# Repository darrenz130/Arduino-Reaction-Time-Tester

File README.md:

<h1>Arduino Reaction Time Tester PCB Design</h1>

<h2>Overview</h2>

<p>
This project is an Arduino-based reaction time testing system designed to measure human response speed with millisecond accuracy. The system uses LEDs as visual stimuli, a push button for user input, and a display to show reaction time results. The firmware is written in C++ and implemented on a custom PCB designed in KiCad.
</p>

<h2>Project Walkthrough</h2>

<h3>1. Breadboard Prototype</h3>

<p>
The initial version of the circuit was built and tested on a breadboard to validate functionality. This phase focused on verifying LED triggering, button input detection, and reaction timing accuracy.
</p>

<h3>2. Firmware Development</h3>

<p>
The system was programmed in C++ using the Arduino IDE. The code handles randomized LED stimulus timing, button press detection, and calculates reaction time in milliseconds using precise timing functions.
</p>

<h3>3. Schematic Design</h3>

<p>
A full circuit schematic was created in KiCad to define the electrical connections between the Arduino, LEDs, button, and display.
</p>

<h3>4. PCB Design</h3>

<p>
A custom PCB shield was designed in KiCad to replace the breadboard setup. This reduced wiring complexity, improved reliability, and created a compact final hardware design.
</p>

<p>
Custom footprints were created where required to match exact component dimensions. This included a potentiometer footprint due to the lack of an existing library part with the correct physical spacing, as well as a custom footprint for the display LED to ensure proper fit and alignment.
</p>

<h2>Languages and Tools Used</h2>

<ul>
  <li>C++</li>
  <li>Arduino IDE</li>
  <li>KiCad (PCB Design)</li>
  <li>Breadboard Prototyping</li>
  <li>Multimeter / Circuit Debugging</li>
</ul>

<h2>Files in This Repository</h2>

<ul>
  <li><b>/firmware</b> → Arduino C++ code</li>
  <li><b>/pcb</b> → KiCad schematic and PCB files</li>
  <li><b>/images</b> → Project screenshots and renders</li>
</ul>

<h2>Demo</h2>

<p>
A short demonstration of the system in action:
<br>
<a href="https://youtu.be/OleBV9ndicw?si=QzNY1ve2LQjAxAnz">
Watch Demo Video
</a>
</p>

<h2>Key Features</h2>

<ul>
  <li>Millisecond-level reaction time measurement</li>
  <li>Randomized LED stimulus timing</li>
  <li>Custom PCB shield for improved reliability</li>
  <li>Fully tested breadboard prototype before final design</li>
</ul>

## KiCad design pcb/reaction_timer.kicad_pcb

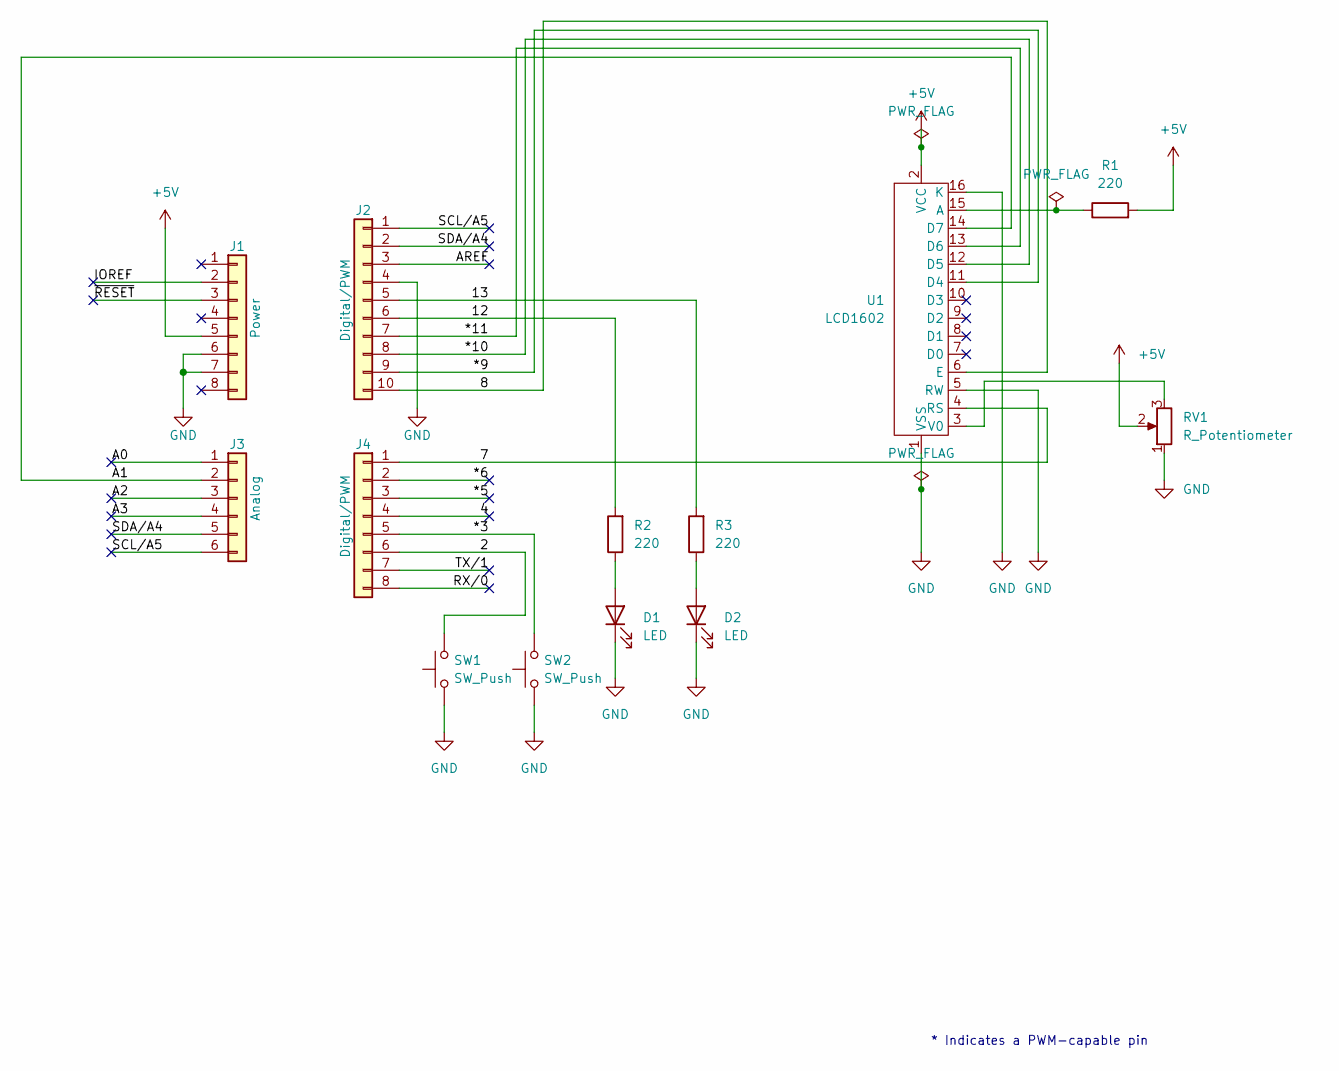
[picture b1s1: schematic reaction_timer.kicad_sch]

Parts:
D1, D2: LED; LED_D5.0mm
J1: Power; PinSocket_1x08_P2.54mm_Vertical
J2: Digital/PWM; PinSocket_1x10_P2.54mm_Vertical
J3: Analog; PinSocket_1x06_P2.54mm_Vertical
J4: Digital/PWM; PinSocket_1x08_P2.54mm_Vertical
R1, R2, R3: 220; R_Axial_DIN0207_L6.3mm_D2.5mm_P7.62mm_Horizontal
RV1: R_Potentiometer; 10k potentiameter
SW1, SW2: SW_Push; SW_PUSH_6mm
U1: LCD1602; PinSocket_1x16_P2.54mm_Vertical

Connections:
+5V: J1.5, R1.2, RV1.2, U1.2 (VCC)
/2: J4.6, SW1.2
/4: J4.4
/7: J4.1, U1.4 (RS)
/8: J2.10, U1.6 (E)
/12: J2.6, R2.2
/13: J2.5, R3.2
/*3: J4.5, SW2.2
/*5: J4.3
/*6: J4.2
/*9: J2.9, U1.11 (D4)
/*10: J2.8, U1.12 (D5)
/*11: J2.7, U1.13 (D6)
/A0: J3.1
/A1: J3.2, U1.14 (D7)
/A2: J3.3
/A3: J3.4
/AREF: J2.3
/IOREF: J1.2
/RX/0: J4.8
/SCL/A5: J2.1, J3.6
/SDA/A4: J2.2, J3.5
/TX/1: J4.7
/~RESET: J1.3
GND: D1.1 (K), D2.1 (K), J1.6, J1.7, J2.4, RV1.1, SW1.1, SW2.1, U1.1 (VSS), U1.5 (RW), U1.16 (K)
unnamed: D1.2 (A), R2.1
unnamed: D2.2 (A), R3.1
unnamed: R1.1, U1.15 (A)
unnamed: RV1.3, U1.3 (V0)

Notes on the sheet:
* Indicates a PWM-capable pin

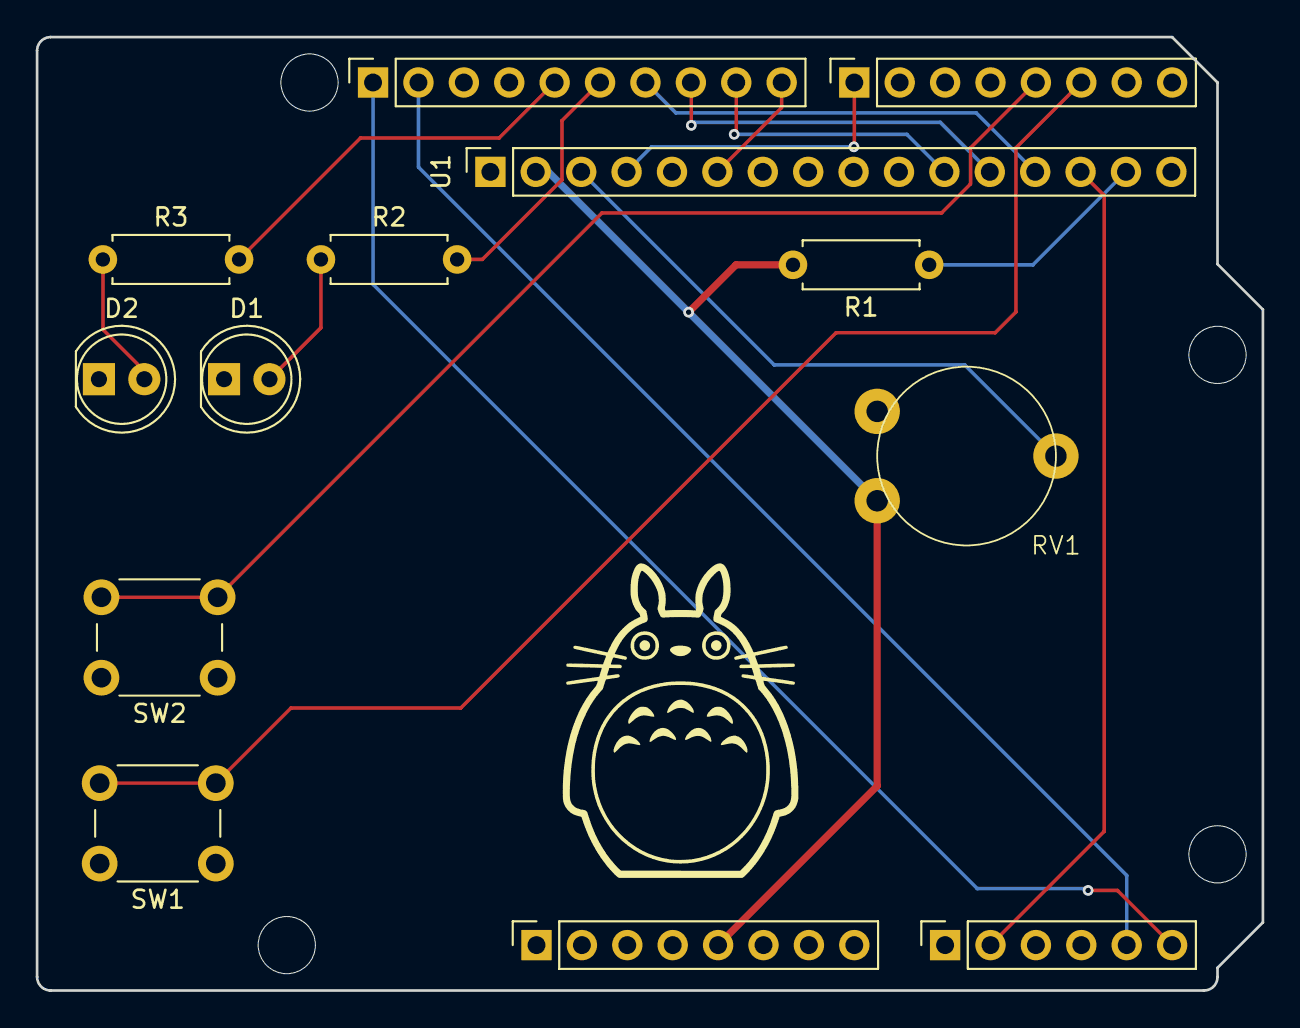
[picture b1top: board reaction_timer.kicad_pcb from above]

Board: 2 copper layers, 68.6 x 53.3 mm, 17 parts (0 on the bottom side), 18 nets.

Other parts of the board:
MH1, MH2, MH3, MH4: MountingHole_3.2mm

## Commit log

2026-05-15 Enhance README with project details and tools
    Added detailed project description and technologies used.
2026-05-15 Create Firmware
2026-05-15 Revise README for clarity and additional details
    Updated the README to enhance project description and structure.
2026-05-15 Rename PCB.png to PCB_Routing.png
2026-05-15 Create schematic
2026-05-16 Enhance PCB Design section with custom footprints info
    Added details about custom footprints created for components in PCB design.
2026-05-16 Remove video demo reference from README
    Removed the video demo section from the README.
2026-05-16 Update README with PCB design images
    Added images of PCB schematic, routing, and 3D render to README.
2026-05-16 Add demo video link to README
